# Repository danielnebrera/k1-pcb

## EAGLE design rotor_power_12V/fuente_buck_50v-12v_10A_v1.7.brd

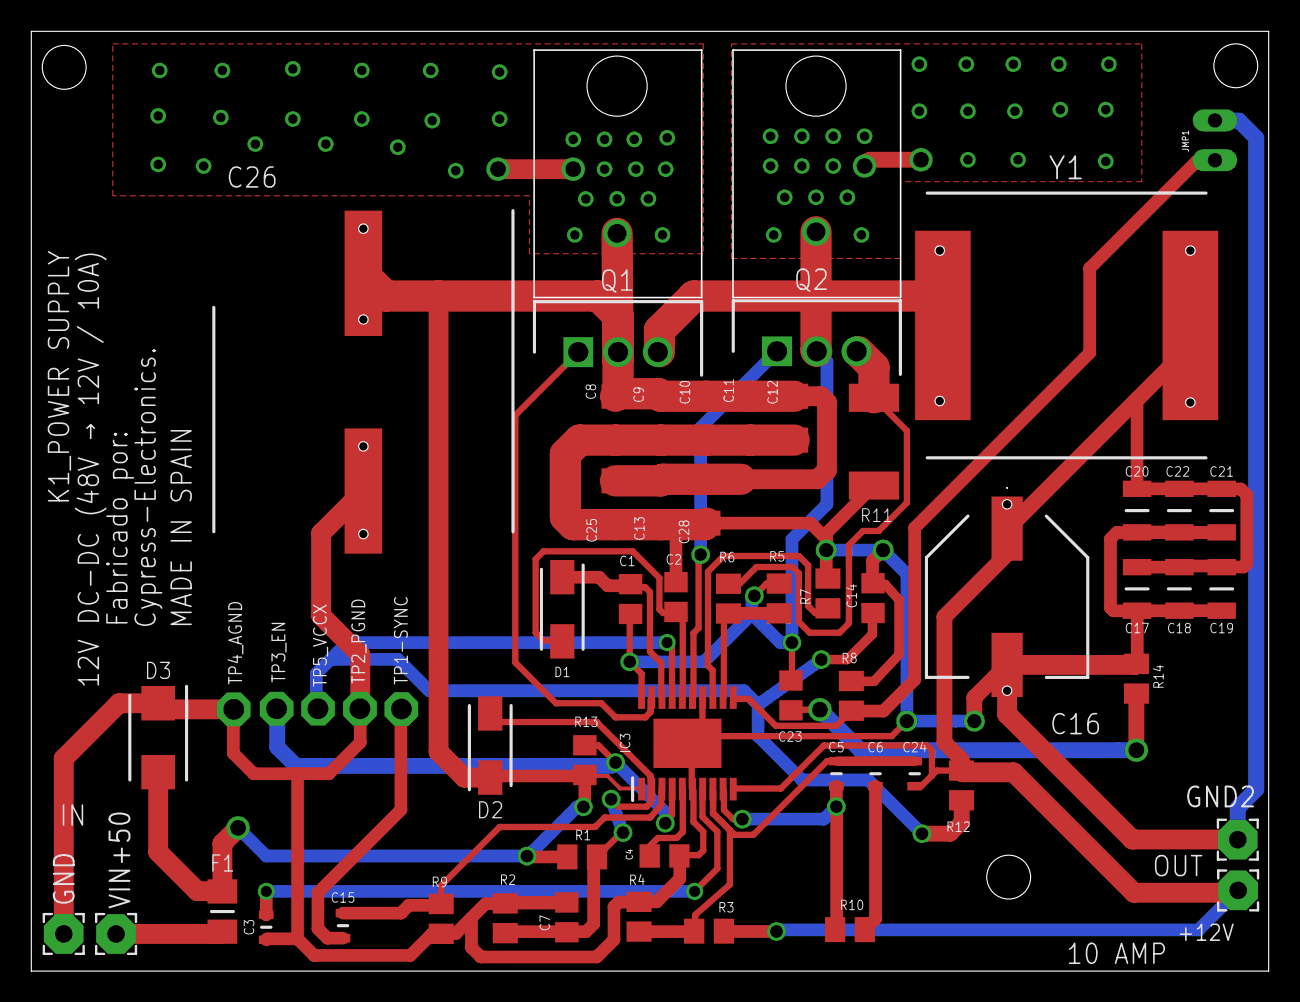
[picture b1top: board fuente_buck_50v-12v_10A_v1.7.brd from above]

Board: 2 copper layers, 79.0 x 60.0 mm, 59 parts (1 on the bottom side), 24 nets.

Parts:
+12V: P3; 2,54/1,1
C1: 0.1uf-x7r _50v; C0805
C2, C14: 1uf_25v; C0805
C3: 0.01uf_50v; CAPC1608X90N
C4: 270PF; C0805
C5, C15: 100pf_50v; CAPC1608X90N
C6: 3300pf_50v; CAPC1608X90N
C7: N/A; C0805
C8, C9, C10, C11: 2.2uf_100v; C1206
C12, C25, C28: 1uf_100v; C1206
C13: 0.1uf_100v; C1206
C16: 330uf 35v; EEE0JA152UAP
C17, C18, C19, C20: 2.2uf_35v; CAPC3216X180N
C21, C22: 1uf_35v; CAPC3216X180N
C23: 220pf_50v; C0805
C24: 47pf_50v; CAPC1608X90N
C26: 330uf_100v; CAPAE1910X1750N
D1, D2: SS16-E3_61T; DIOM5127X229N
D3: SMBJ58A; DIOM5436X261N
F1: 8amp_slow blow; FUSC3216X123N
GND: P2; 2,54/1,1
GND2: P4; 2,54/1,1
IC3: LM5116; SOP65P640X110-21N
JMP1: JP1
Q1, Q2: CSD19506KCS; TO254P470X1016X1611-3P
R1: 56k; M0805
R2: 21k; M0805
R3: 10.7 kΩ; M0805
R4: 1.21 kΩ; M0805
R5: 5.1Ω; M0805
R6: 4.7Ω; M0805
R7: 0; M0805
R8: 10k; M0805
R9: 12.4k; M0805
R10: 18K; M0805
R11: 0.0068Ω; R2512
R12: N/A; M0805
R13: 100k; R0805
R14: 10Ω; M0805
TP1-SYNC: TP1; P1-13
TP2_PGND, TP3_EN, TP4_AGND, TP5_VCCX: TPPAD1-13; P1-13
VIN+50: P1; 2,54/1,1
Y1: AMDLA1707S-150MT; INDPM178169X700N

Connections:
10K: C2.1, D1.2, IC3.16
GND: C2.2, C3.2, C4.2, C7.2, C8.2, C9.2, C10.2, C11.2, C12.2, C13.2, C14.1, C16.2, C17.1, C18.1, C19.1, C20.1, C21.1, C22.1, C25.2, C26.2, C28.2, D3.1, GND.1, GND2.1, IC3.6, IC3.14, IC3.21, JMP1.1, R2.1, R4.1, R7.2, R8.2, R9.1, R11.1, R14.1, TP2_PGND.TP, TP4_AGND.TP
unnamed: C5.1, C6.1, C24.1, IC3.8, R3.2, R4.2
unnamed: F1.1, VIN+50.1
unnamed: C23.2, R14.2
unnamed: C7.1, D2.2, IC3.2, R1.1, R2.2
unnamed: C15.1, IC3.3, R9.2
unnamed: C15.2, TP1-SYNC.TP
unnamed: C4.1, IC3.5
unnamed: C3.1, IC3.7
unnamed: C14.2, IC3.17, R12.1, TP5_VCCX.TP
unnamed: C5.2, IC3.9, R10.2
unnamed: IC3.19, Q1.1
unnamed: C6.2, R10.1
unnamed: +12V.1, C16.1, C17.2, C18.2, C19.2, C20.2, C21.2, C22.2, C24.2, IC3.10, R3.1, R12.2, Y1.2
unnamed: IC3.4, R13.1, TP3_EN.TP
unnamed: IC3.15, Q2.1
unnamed: C1.2, D1.1, IC3.18
unnamed: IC3.13, R7.1
unnamed: Q2.3, R6.2, R11.2
unnamed: IC3.11, JMP1.2, R8.1
unnamed: IC3.12, R5.1, R6.1
SW: C1.1, C23.1, IC3.20, Q1.3, Q2.2, R5.2, Y1.1
VIN: C8.1, C9.1, C10.1, C11.1, C12.1, C13.1, C25.1, C26.1, C28.1, D2.1, D3.2, F1.2, IC3.1, Q1.2, R1.2, R13.2

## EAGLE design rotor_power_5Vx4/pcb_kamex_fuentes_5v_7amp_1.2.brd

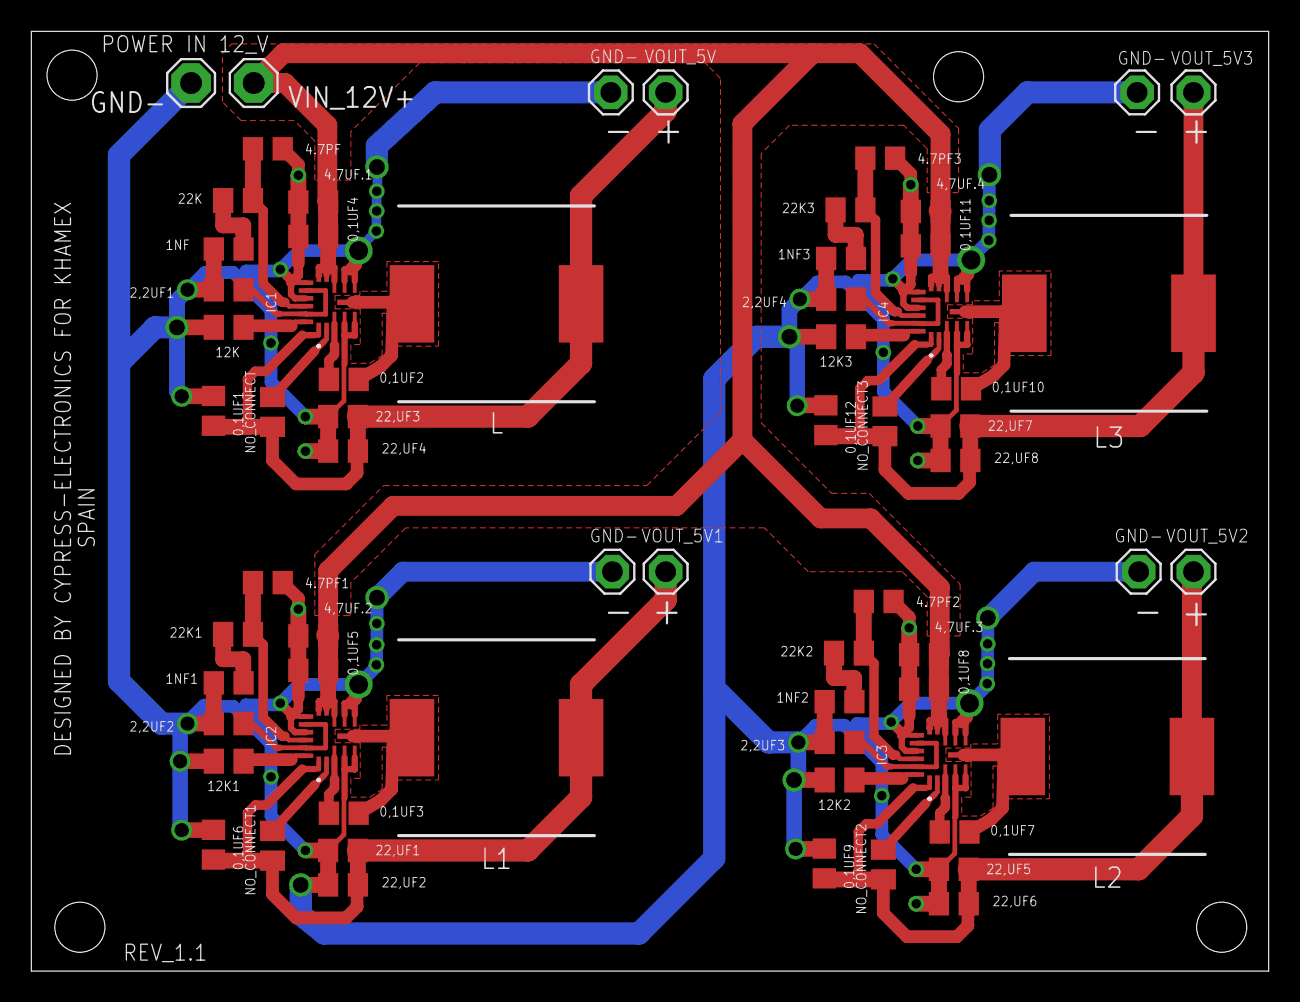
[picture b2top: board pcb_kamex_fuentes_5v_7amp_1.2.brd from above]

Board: 2 copper layers, 79.0 x 60.0 mm, 66 parts (0 on the bottom side), 34 nets.

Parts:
0,1UF1, 0,1UF2, 0,1UF3, 0,1UF4, 0,1UF5, 0,1UF6, 0,1UF7, 0,1UF8, 0,1UF9, 0,1UF10, 0,1UF11, 0,1UF12: 0.1uF_50-V; C0805
1NF, 1NF1, 1NF2, 1NF3: 1nf_50-V; C0805
2,2UF1, 2,2UF2, 2,2UF3, 2,2UF4: 2,2uf_10-V; C0805
4,7UF.1, 4,7UF.2, 4,7UF.3, 4,7UF.4: 4,7uf_50-V; C0805
4.7PF, 4.7PF1, 4.7PF2, 4.7PF3: 4.7pf_50-V; C0805
12K, 12K1, 12K2, 12K3: 12k_50v; M0805
22,UF1, 22,UF2, 22,UF3, 22,UF4, 22,UF5, 22,UF6, 22,UF7, 22,UF8: 22uf_10-V; C0805
22K, 22K1, 22K2, 22K3: 22k_50v; M0805
GND: SE13
GND-: SE14
IC1, IC2, IC3, IC4: MAX20008AFOC_VY+T; MAX20008AFOCVYT
L, L1, L2, L3: DR125-1R0-R; INDPM125125X600N
LSP6, LSP7, LSP8, LSP9, LSP10: SE13
NO_CONNECT, NO_CONNECT1, NO_CONNECT2, NO_CONNECT3: 10k_50-V; M0805
VIN_12V+: SE14
VOUT_5V, VOUT_5V3: SE13

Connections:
BIAS: 2,2UF1.1, IC1.13, IC1.16
BIAS1: 2,2UF2.1, IC2.13, IC2.16
BIAS2: 2,2UF3.1, IC3.13, IC3.16
BIAS3: 2,2UF4.1, IC4.13, IC4.16
BST: 0,1UF2.2, IC1.3
BST1: 0,1UF3.2, IC2.3
BST2: 0,1UF7.2, IC3.3
BST3: 0,1UF10.2, IC4.3
COM: 4.7PF.1, 22K.1, IC1.15
COM1: 4.7PF1.1, 22K1.1, IC2.15
COM2: 4.7PF2.1, 22K2.1, IC3.15
COM3: 4.7PF3.1, 22K3.1, IC4.15
GND: 0,1UF1.1, 0,1UF4.1, 0,1UF5.1, 0,1UF6.1, 0,1UF8.1, 0,1UF9.1, 0,1UF11.1, 0,1UF12.1, 1NF.1, 1NF1.1, 1NF2.1, 1NF3.1, 2,2UF1.2, 2,2UF2.2, 2,2UF3.2, 2,2UF4.2, 4,7UF.1.1, 4,7UF.2.1, 4,7UF.3.1, 4,7UF.4.1, 4.7PF.2, 4.7PF1.2, 4.7PF2.2, 4.7PF3.2, 12K.2, 12K1.2, 12K2.2, 12K3.2, 22,UF1.1, 22,UF2.1, 22,UF3.1, 22,UF4.1, 22,UF5.1, 22,UF6.1, 22,UF7.1, 22,UF8.1, GND.MP, GND-.MP, IC1.4, IC1.5, IC1.7, IC1.8, IC1.12, IC1.14, IC2.4, IC2.5, IC2.7, IC2.8, IC2.12, IC2.14, IC3.4, IC3.5, IC3.7, IC3.8, IC3.12, IC3.14, IC4.4, IC4.5, IC4.7, IC4.8, IC4.12, IC4.14, LSP6.MP, LSP8.MP, LSP10.MP
unnamed: 12K1.1, IC2.17
unnamed: 1NF.2, 22K.2
unnamed: 0,1UF3.1, IC2.6, L1.1
unnamed: IC2.2, NO_CONNECT1.1
unnamed: 1NF1.2, 22K1.2
unnamed: 12K.1, IC1.17
unnamed: 12K2.1, IC3.17
unnamed: 0,1UF7.1, IC3.6, L2.1
unnamed: 0,1UF2.1, IC1.6, L.1
unnamed: IC1.2, NO_CONNECT.1
unnamed: IC3.2, NO_CONNECT2.1
unnamed: 1NF2.2, 22K2.2
unnamed: 12K3.1, IC4.17
unnamed: 0,1UF10.1, IC4.6, L3.1
unnamed: IC4.2, NO_CONNECT3.1
unnamed: 1NF3.2, 22K3.2
VIN_12V: 0,1UF4.2, 0,1UF5.2, 0,1UF8.2, 0,1UF11.2, 4,7UF.1.2, 4,7UF.2.2, 4,7UF.3.2, 4,7UF.4.2, IC1.9, IC1.10, IC1.11, IC2.9, IC2.10, IC2.11, IC3.9, IC3.10, IC3.11, IC4.9, IC4.10, IC4.11, VIN_12V+.MP
VOUT_5V: 0,1UF1.2, 22,UF3.2, 22,UF4.2, IC1.1, L.2, NO_CONNECT.2, VOUT_5V.MP
VOUT_5V1: 0,1UF6.2, 22,UF1.2, 22,UF2.2, IC2.1, L1.2, LSP7.MP, NO_CONNECT1.2
VOUT_5V2: 0,1UF9.2, 22,UF5.2, 22,UF6.2, IC3.1, L2.2, LSP9.MP, NO_CONNECT2.2
VOUT_5V3: 0,1UF12.2, 22,UF7.2, 22,UF8.2, IC4.1, L3.2, NO_CONNECT3.2, VOUT_5V3.MP

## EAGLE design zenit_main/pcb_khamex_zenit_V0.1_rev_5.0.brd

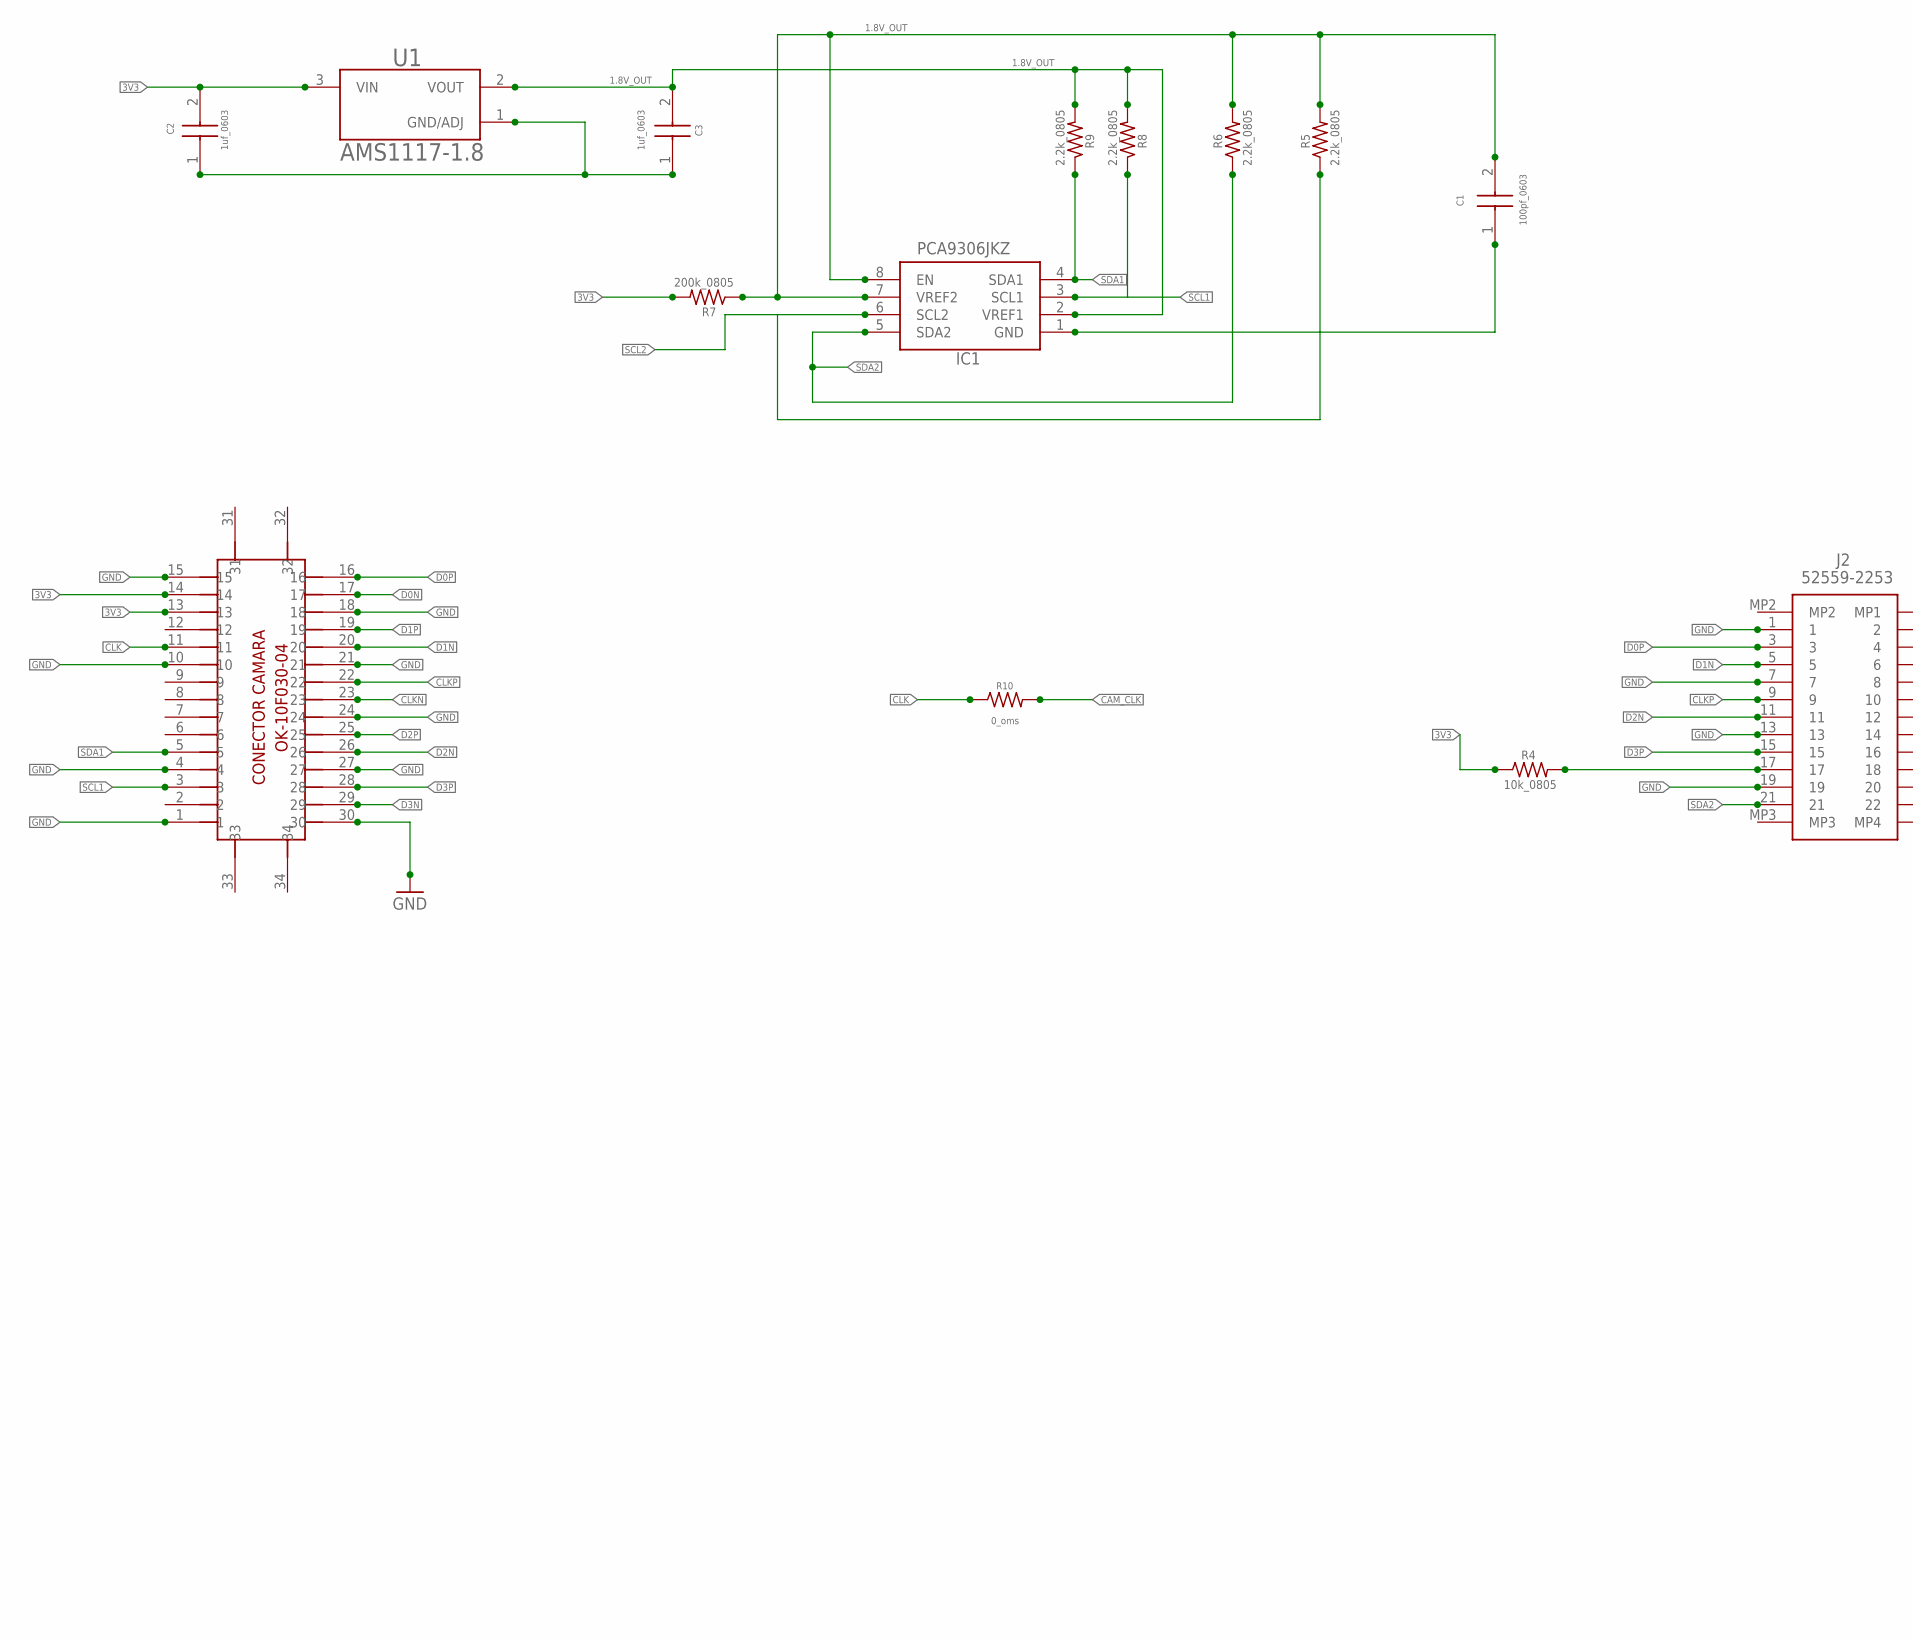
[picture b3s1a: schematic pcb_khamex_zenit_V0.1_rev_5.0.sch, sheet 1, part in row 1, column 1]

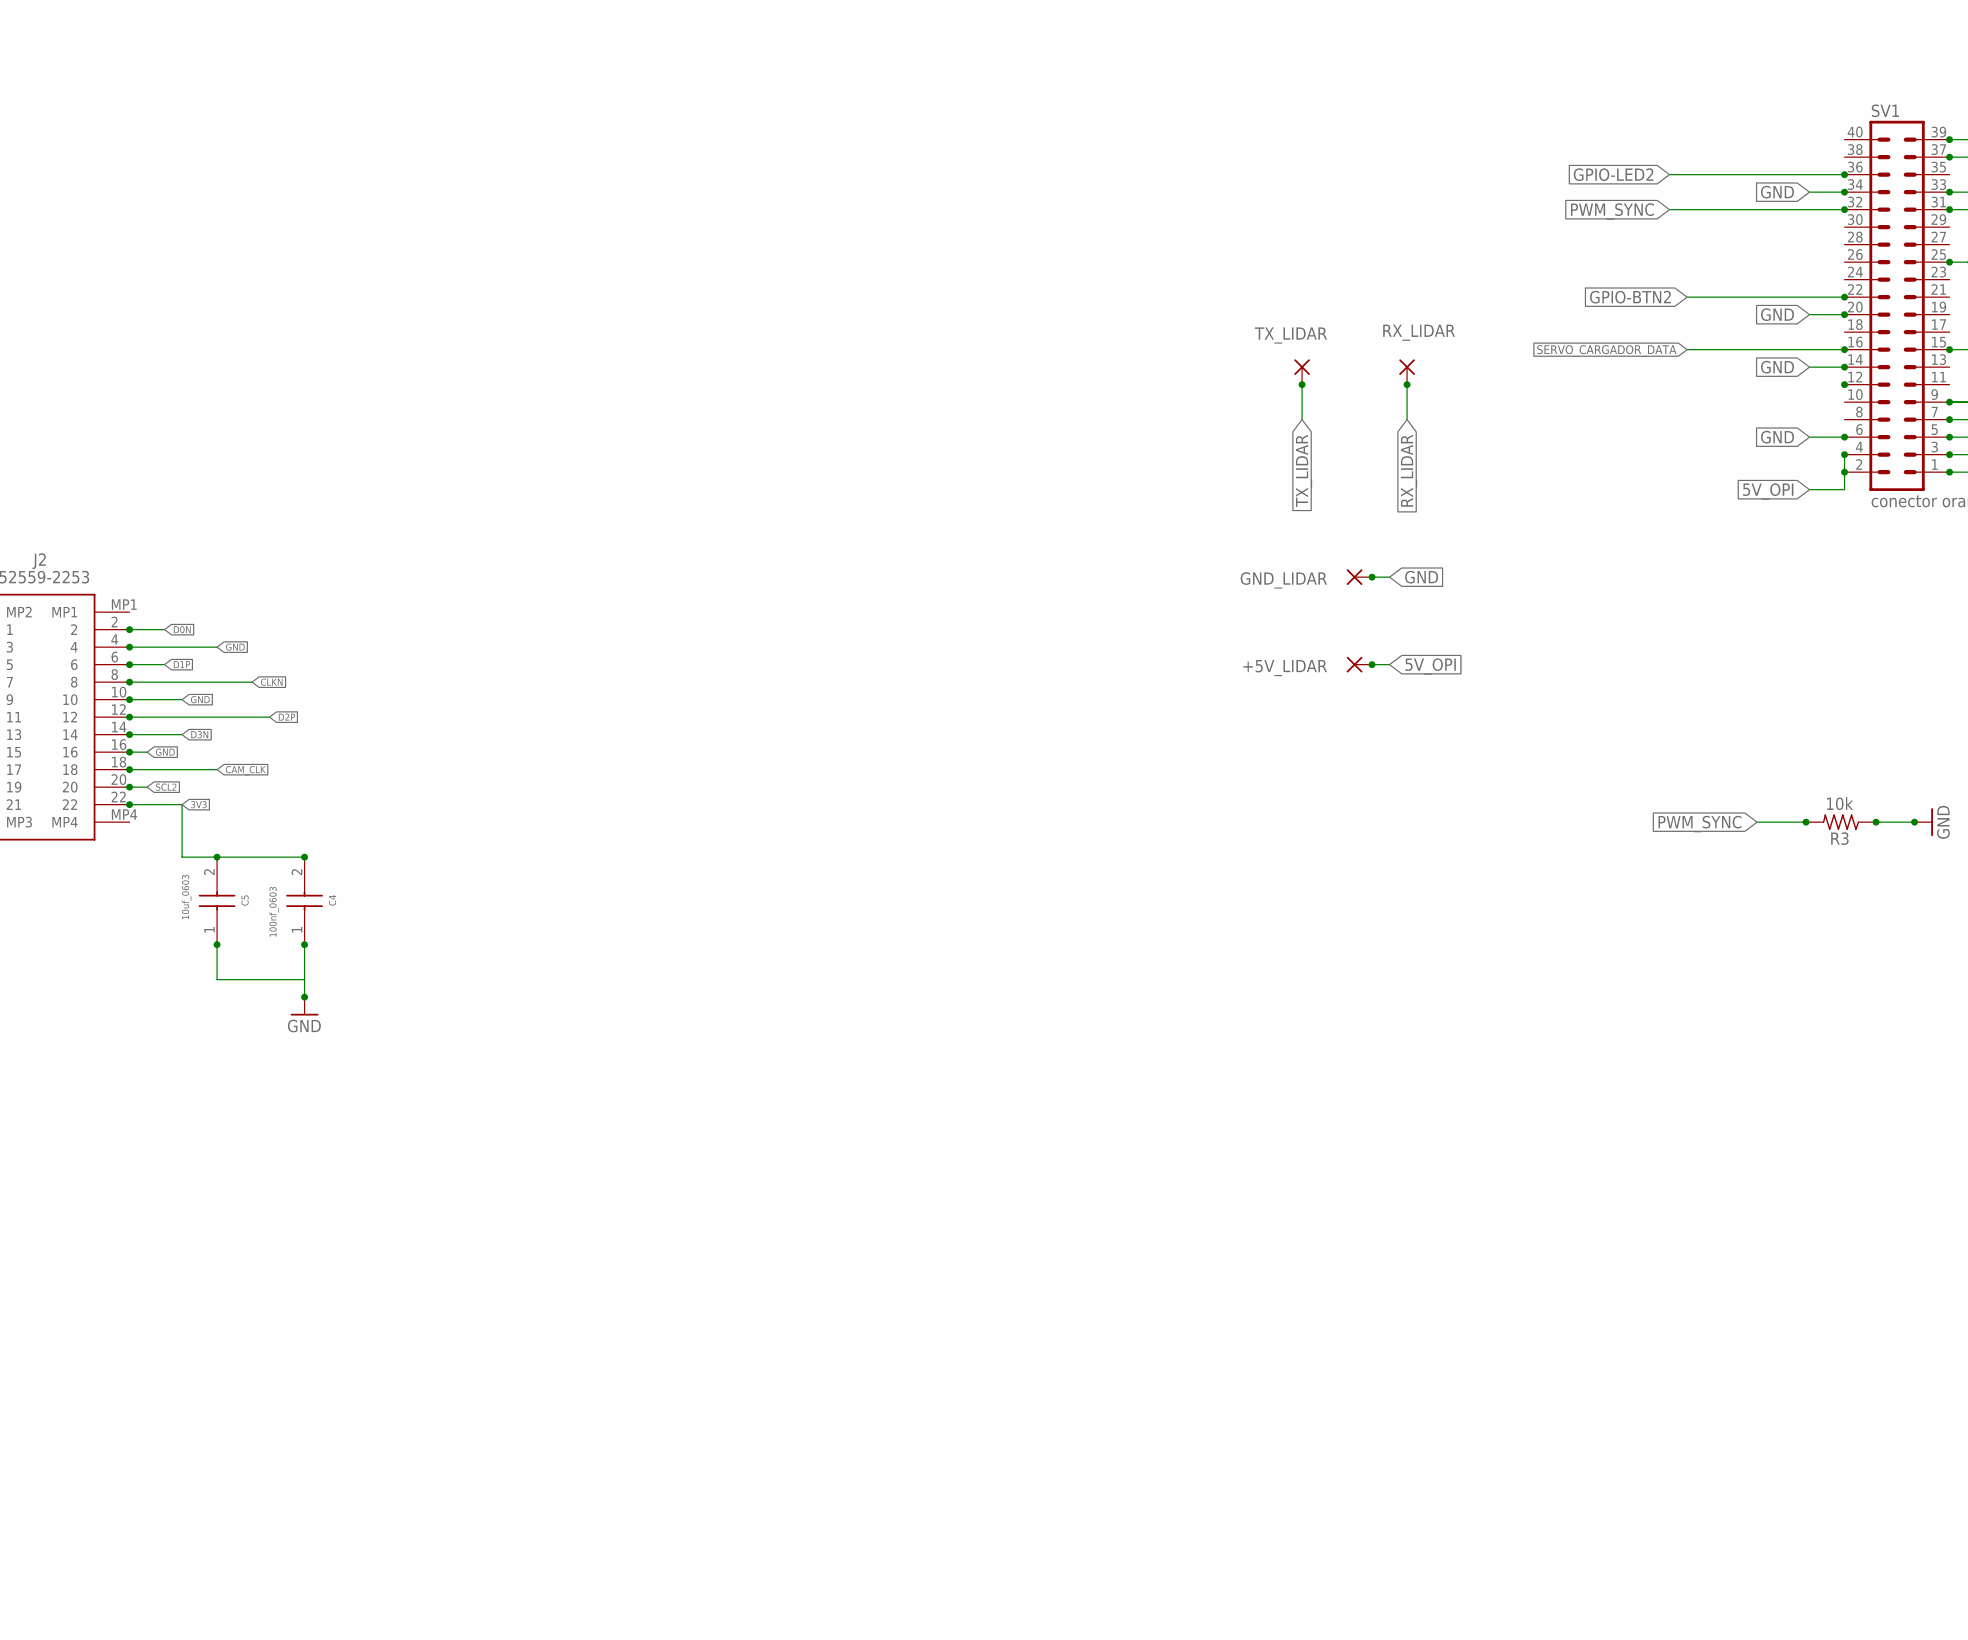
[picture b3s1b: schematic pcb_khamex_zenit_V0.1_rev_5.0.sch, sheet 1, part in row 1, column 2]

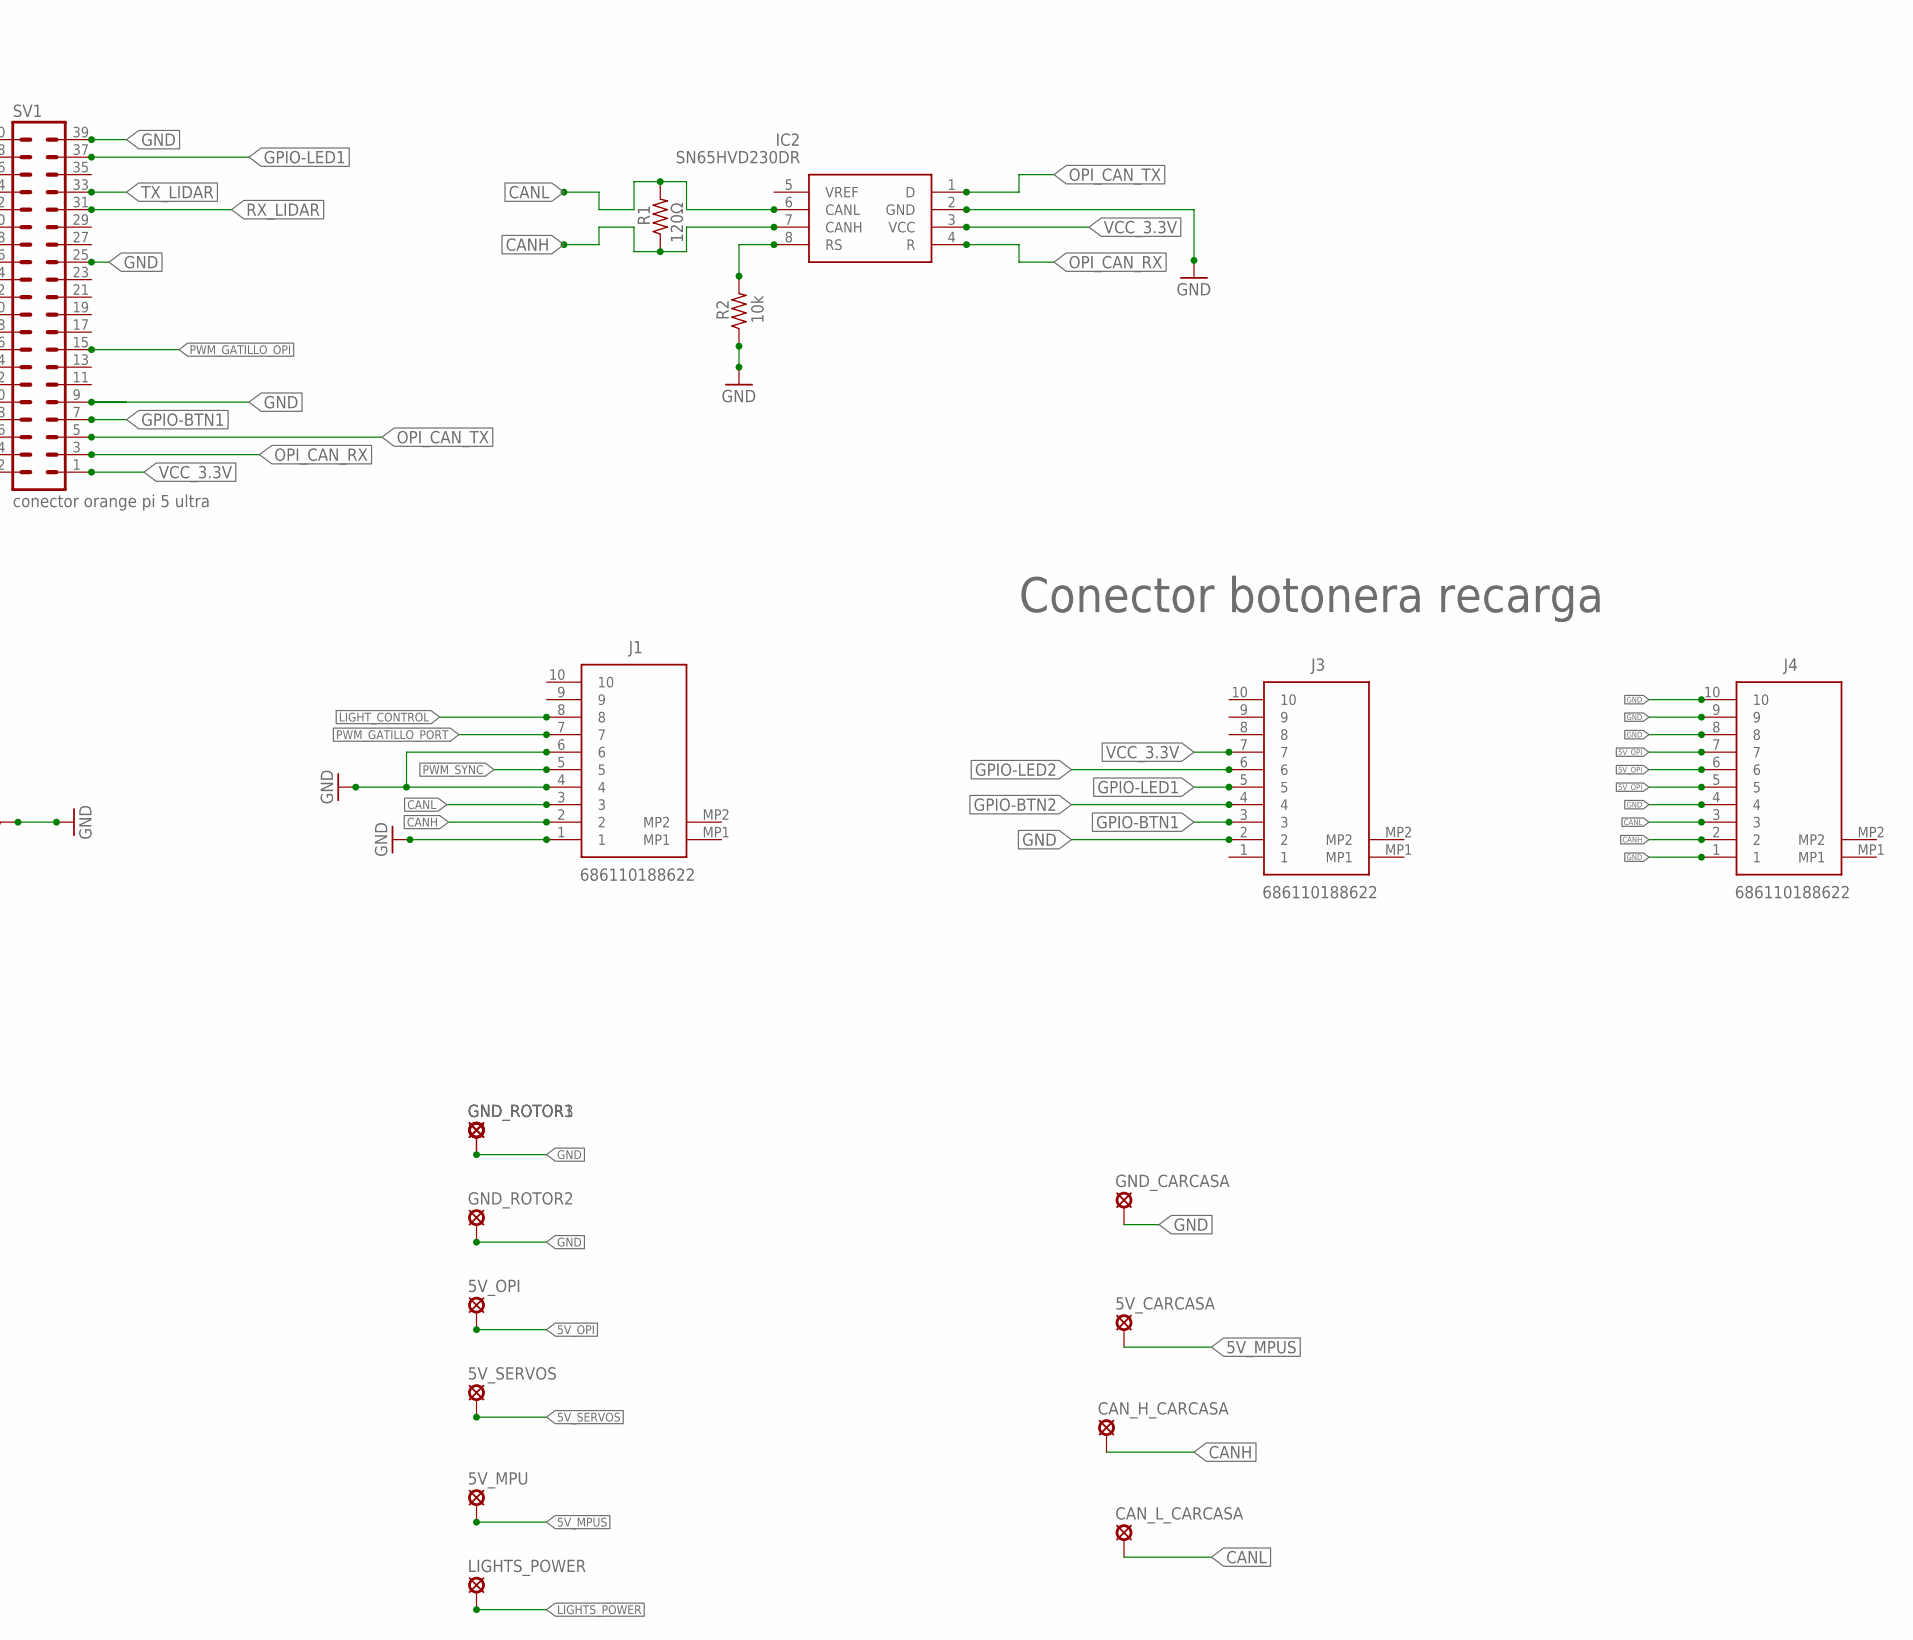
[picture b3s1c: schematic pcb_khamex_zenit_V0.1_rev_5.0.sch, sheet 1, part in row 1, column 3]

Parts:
5V_CARCASA, 5V_MPU, 5V_OPI, 5V_SERVOS: SE14
+5V_LIDAR: WIREPAD1,6/0,8; 1,6/0,8
C1: 100pf_0603; CAPC1608X90N
C2, C3: 1uf_0603; CAPC1608X90N
C4: 100nf_0603; CAPC1608X90N
C5: 10uf_0603; CAPC1608X90N
CAN_H_CARCASA: SE14
CAN_L_CARCASA: SE14
GND_CARCASA: SE14
GND_LIDAR: WIREPAD1,6/0,8; 1,6/0,8
GND_ROTOR1, GND_ROTOR2, GND_ROTOR3: SE14
IC1: PCA9306JKZ
IC2: SN65HVD230DR; SOT127P600X175-8N
J1, J3, J4: 686110188622
J2: 52559-2253; 525592253
LIGHTS_POWER: SE14
R1: 120Ω; M0805
R2: 10k; M0805
R3: 10k; R0603
R4: 10k_0805; M0805
R5, R6, R8, R9: 2.2k_0805; M0805
R7: 200k_0805; M0805
R10: 0_oms; M0805
RX_LIDAR: WIREPAD1,6/0,8; 1,6/0,8
SV1: conector orange pi 5 ultra; MA20-2
TX_LIDAR: WIREPAD1,6/0,8; 1,6/0,8
U1: AMS1117-1.8; SOT229P700X180-4N
U$1: OK-10F030-04_DEVICE; OK-10F030-04_PACKAGE

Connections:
3V3: C2.2, C4.2, C5.2, J2.22, R4.1, R7.2, U1.3 (VIN), U$1.13, U$1.14
5V_MPUS: 5V_CARCASA.MP, 5V_MPU.MP
5V_OPI: 5V_OPI.MP, +5V_LIDAR.1, J4.5, J4.6, J4.7, SV1.2, SV1.4
5V_SERVOS: 5V_SERVOS.MP; also elsewhere on the board
CAM_CLK: J2.18, R10.2
CANH: CAN_H_CARCASA.MP, IC2.7 (CANH), J1.2, J4.2, R1.1
CANL: CAN_L_CARCASA.MP, IC2.6 (CANL), J1.3, J4.3, R1.2
CLK: R10.1, U$1.11
CLKN: J2.8, U$1.23
CLKP: J2.9, U$1.22
D0N: J2.2, U$1.17
D0P: J2.3, U$1.16
D1N: J2.5, U$1.20
D1P: J2.6, U$1.19
D2N: J2.11, U$1.26
D2P: J2.12, U$1.25
D3N: J2.14, U$1.29
D3P: J2.15, U$1.28
GND: C4.1, C5.1, GND_CARCASA.MP, GND_LIDAR.1, GND_ROTOR1.MP, GND_ROTOR2.MP, GND_ROTOR3.MP, IC2.2 (GND), J1.1, J1.4, J1.6, J2.1, J2.4, J2.7, J2.10, J2.13, J2.16, J2.19, J3.2, J4.1, J4.4, J4.8, J4.9, J4.10, R2.1, R3.1, SV1.6, SV1.9, SV1.14, SV1.20, SV1.25, SV1.34, SV1.39, U$1.1, U$1.4, U$1.10, U$1.15, U$1.18, U$1.21, U$1.24, U$1.27, U$1.30; also elsewhere on the board
GPIO-BTN1: J3.3, SV1.7
GPIO-BTN2: J3.4, SV1.22
GPIO-LED1: J3.5, SV1.37
GPIO-LED2: J3.6, SV1.36
LIGHTS_POWER: LIGHTS_POWER.MP
LIGHT_CONTROL: J1.8
unnamed: C1.1, IC1.1 (GND)
unnamed: C1.2, IC1.7 (VREF2), IC1.8 (EN), R5.2, R6.2, R7.1
unnamed: J2.17, R4.2
unnamed: C2.1, C3.1, U1.1 (GND/ADJ)
unnamed: C3.2, IC1.2 (VREF1), R8.2, R9.2, U1.2 (VOUT)
unnamed: IC2.8 (RS), R2.2
OPI_CAN_RX: IC2.4 (R), SV1.3
OPI_CAN_TX: IC2.1 (D), SV1.5
PWM_GATILLO_OPI: SV1.15; also elsewhere on the board
PWM_GATILLO_PORT: J1.7; also elsewhere on the board
PWM_SYNC: J1.5, R3.2, SV1.32
RX_LIDAR: RX_LIDAR.1, SV1.31
SCL1: IC1.3 (SCL1), R8.1, U$1.3
SCL2: IC1.6 (SCL2), J2.20, R5.1
SDA1: IC1.4 (SDA1), R9.1, U$1.5
SDA2: IC1.5 (SDA2), J2.21, R6.1
SERVO_CARGADOR_DATA: SV1.16; also elsewhere on the board
TX_LIDAR: SV1.33, TX_LIDAR.1
VCC_3.3V: IC2.3 (VCC), J3.7, SV1.1

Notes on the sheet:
Conector botonera recarga
1.8V_OUT

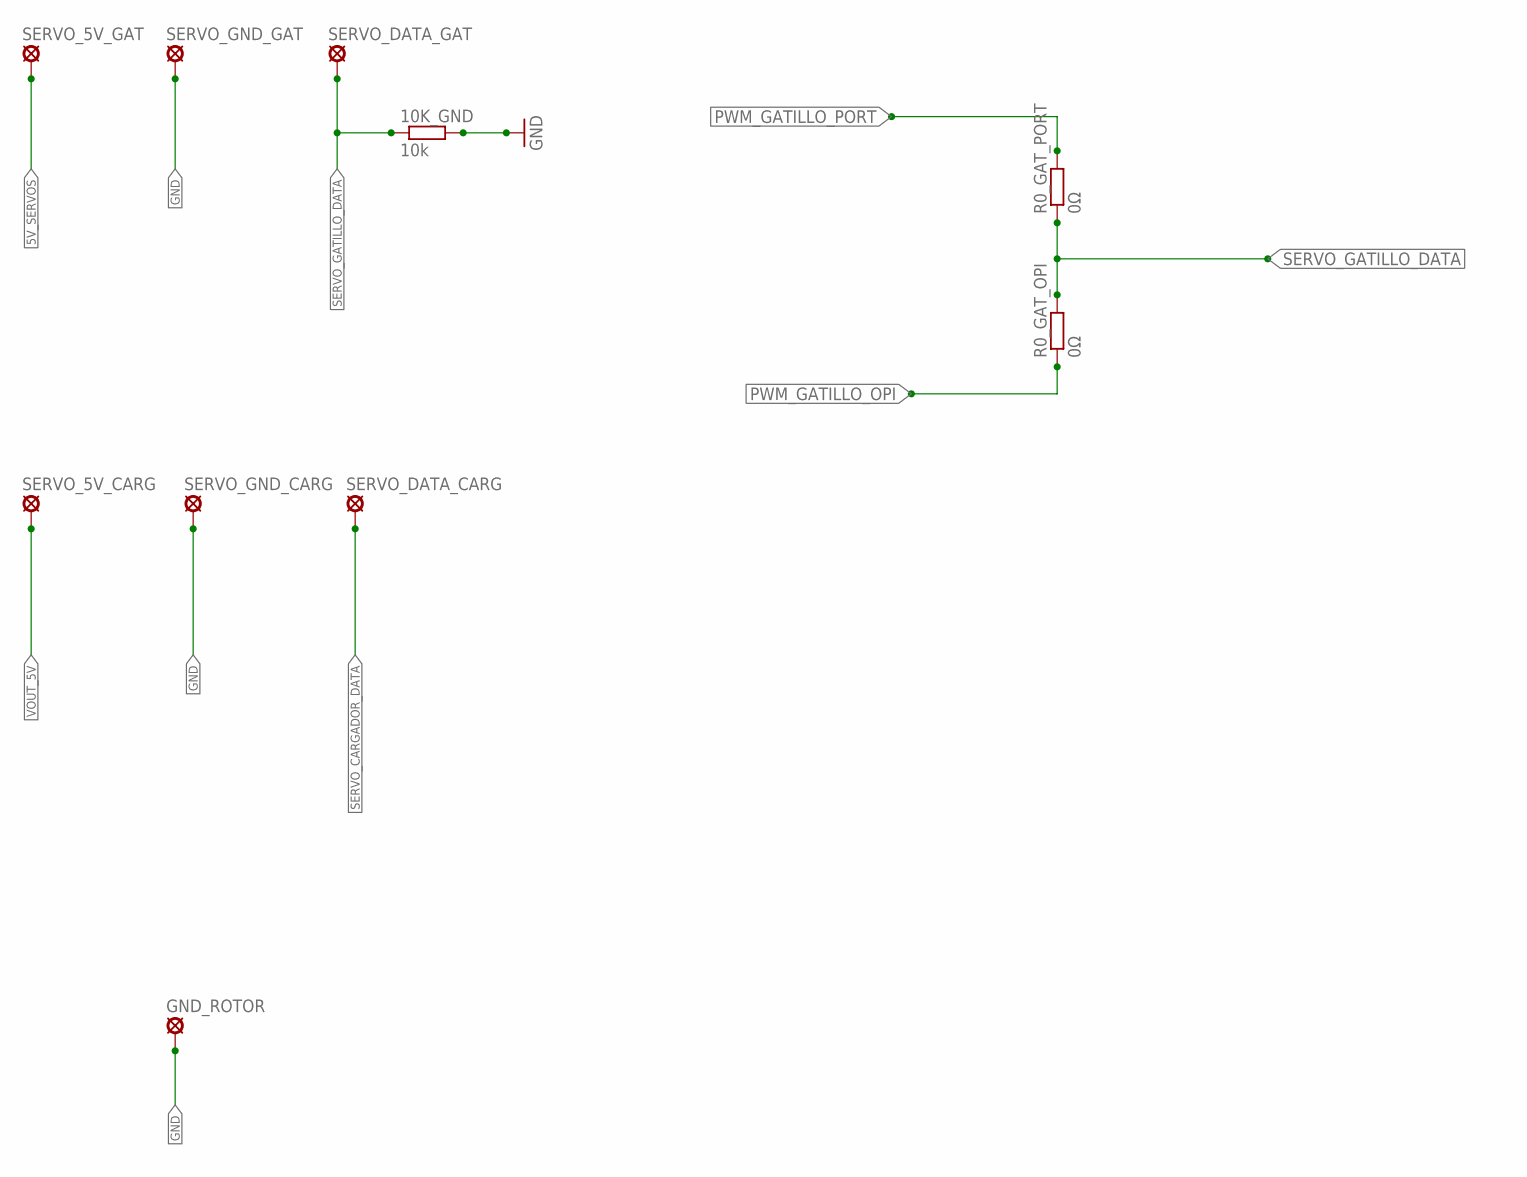
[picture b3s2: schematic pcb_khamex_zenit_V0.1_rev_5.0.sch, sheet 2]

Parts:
10K_GND: 10k; R0603
GND_ROTOR: SE14
R0_GAT_OPI, R0_GAT_PORT: 0Ω; R0603
SERVO_5V_CARG, SERVO_5V_GAT: SE14
SERVO_DATA_CARG: SE14
SERVO_DATA_GAT: SE14
SERVO_GND_CARG: SE14
SERVO_GND_GAT: SE14

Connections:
5V_SERVOS: SERVO_5V_GAT.MP; also elsewhere on the board
GND: 10K_GND.2, GND_ROTOR.MP, SERVO_GND_CARG.MP, SERVO_GND_GAT.MP; also elsewhere on the board
PWM_GATILLO_OPI: R0_GAT_OPI.1; also elsewhere on the board
PWM_GATILLO_PORT: R0_GAT_PORT.2; also elsewhere on the board
SERVO_CARGADOR_DATA: SERVO_DATA_CARG.MP; also elsewhere on the board
SERVO_GATILLO_DATA: 10K_GND.1, R0_GAT_OPI.2, R0_GAT_PORT.1, SERVO_DATA_GAT.MP
VOUT_5V: SERVO_5V_CARG.MP

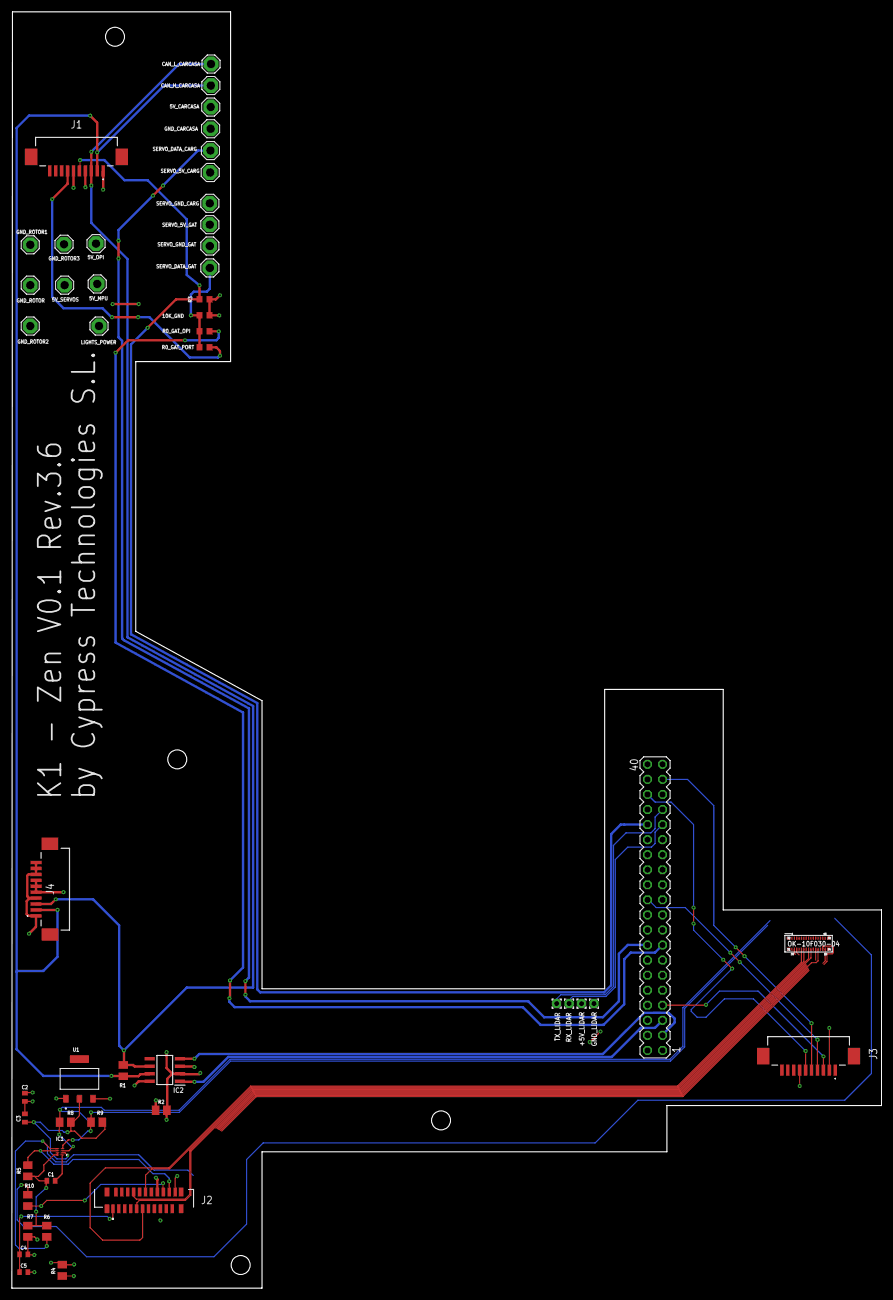
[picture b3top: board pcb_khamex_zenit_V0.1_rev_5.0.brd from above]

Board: 4 copper layers, 146.7 x 215.3 mm, 49 parts (0 on the bottom side), 43 nets.
